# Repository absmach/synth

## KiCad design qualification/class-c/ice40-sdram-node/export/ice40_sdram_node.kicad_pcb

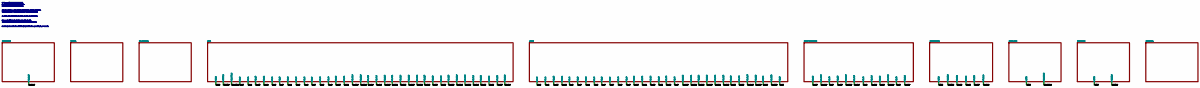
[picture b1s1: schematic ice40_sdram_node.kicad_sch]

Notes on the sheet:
5 V in, max 5.25 V. F1 hold 1.1 A, 16 V.
D1 standoff 6.0 V, above 5.25 V, before Q1.
Q1 P-MOSFET reverse stage, gate to GND.
Soft SDR controller, no hard DDR PHY. VPP_FAST (pin 109) left unconnected.
VCCPLL0/1 from 1.2 V through ferrite L1, 100 nF each and 1 uF bulk.
22 ohm in series at the FPGA end of CLK, CS, RAS, CAS, WE and CKE.
Flash on the iCE40 master SPI pins SS_B, SCK, SDI, SDO.
CRESET_B and CDONE pulled up 10 k. WP and HOLD pulled up 10 k.
D2 3.3 V present. D3 lit when CDONE is high (Q2 buffers the open-drain pin). D4 user LED.

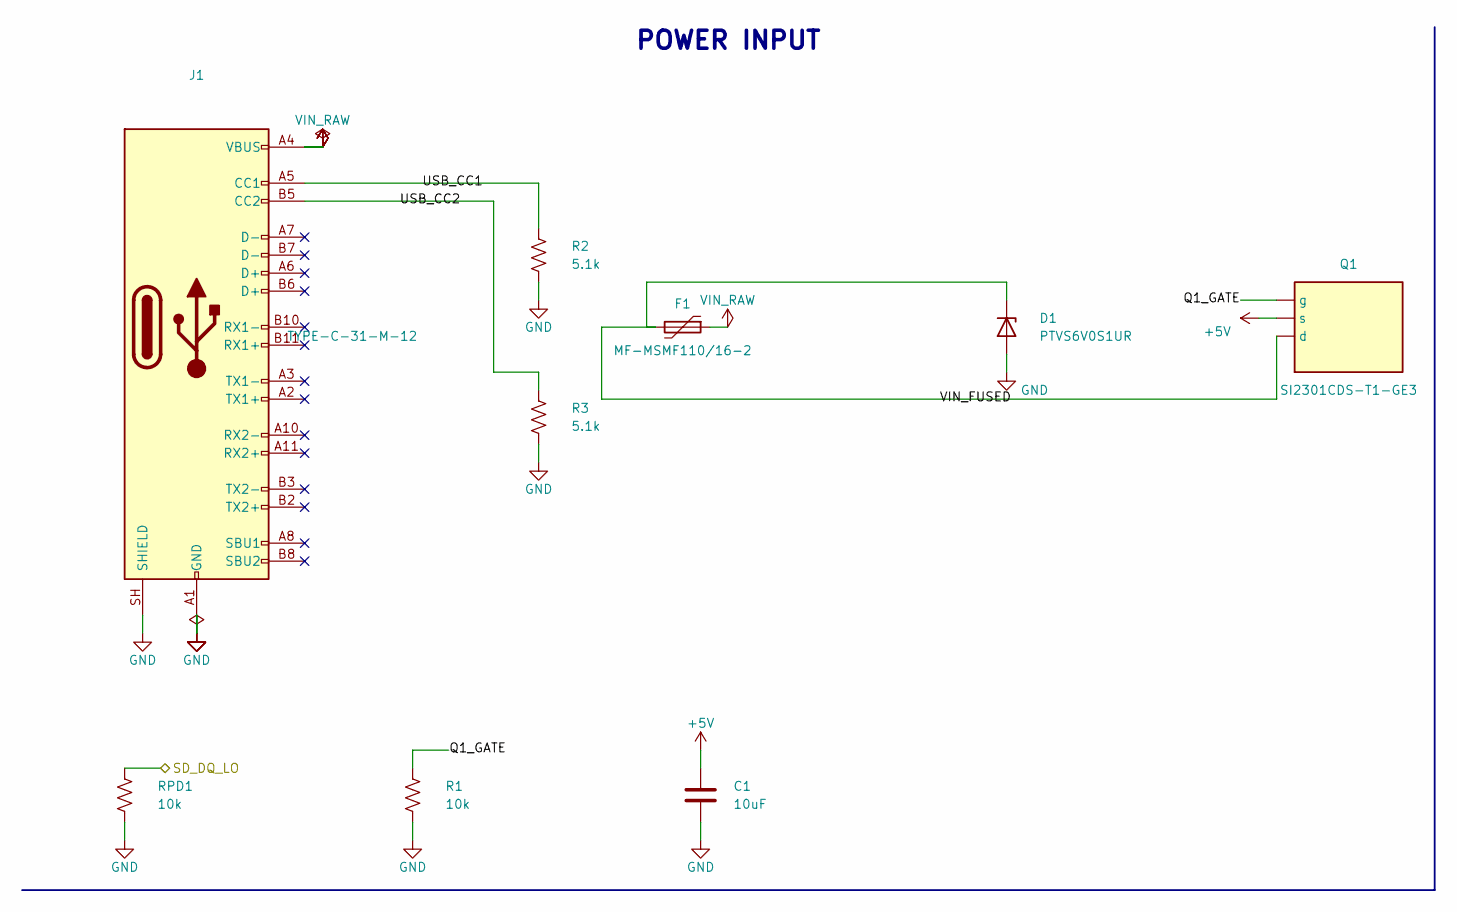
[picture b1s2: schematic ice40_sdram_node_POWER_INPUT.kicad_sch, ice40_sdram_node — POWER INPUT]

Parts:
C1: 10uF; C_0805_2012Metric
D1: PTVS6V0S1UR; Nexperia_CFP3_SOD-123W; MPN PTVS6V0S1UR
F1: MF-MSMF110/16-2; Fuse_1812_4532Metric; MPN MF-MSMF110/16-2; LCSC C210834
J1: TYPE-C-31-M-12; USB_C_Receptacle_HRO_TYPE-C-31-M-12; MPN TYPE-C-31-M-12; LCSC C165948
Q1: SI2301CDS-T1-GE3; SOT-23; MPN SI2301CDS-T1-GE3; LCSC C10487
R1: 10k; R_0603_1608Metric
R2, R3: 5.1k; R_0603_1608Metric
RPD1: 10k; R_0603_1608Metric

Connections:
+5V: C1.1, Q1.2 (s); also elsewhere on the board
GND: C1.2, D1.2 (A), J1.A1 (GND), J1.A12 (GND), J1.B1 (GND), J1.B12 (GND), J1.SH (SHIELD), R1.2, R2.2, R3.2, RPD1.2; also elsewhere on the board
Q1_GATE: Q1.1 (g), R1.1
SD_DQ_LO: RPD1.1; also elsewhere on the board
USB_CC1: J1.A5 (CC1), R2.1
USB_CC2: J1.B5 (CC2), R3.1
VIN_FUSED: D1.1 (K), F1.2, Q1.3 (d)
VIN_RAW: F1.1, J1.A4 (VBUS), J1.A9 (VBUS), J1.B4 (VBUS), J1.B9 (VBUS)

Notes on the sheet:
POWER INPUT

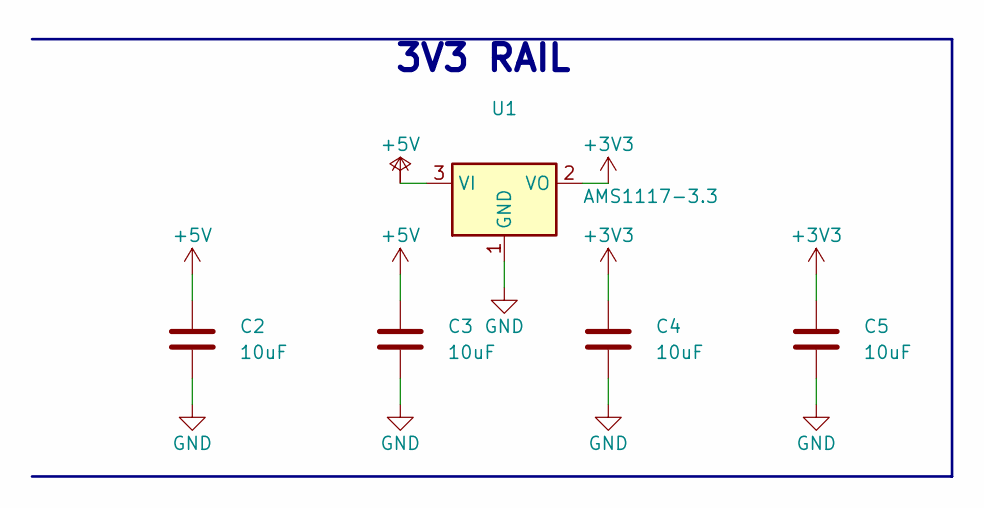
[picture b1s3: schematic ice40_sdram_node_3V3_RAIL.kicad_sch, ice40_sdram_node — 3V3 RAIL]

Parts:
C2, C3, C4, C5: 10uF; C_0805_2012Metric
U1: AMS1117-3.3; SOT-223-3_TabPin2; MPN AMS1117-3.3; LCSC C6186

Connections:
+3V3: C4.1, C5.1, U1.2 (VO); also elsewhere on the board
+5V: C2.1, C3.1, U1.3 (VI); also elsewhere on the board
GND: C2.2, C3.2, C4.2, C5.2, U1.1 (GND); also elsewhere on the board

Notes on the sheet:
3V3 RAIL

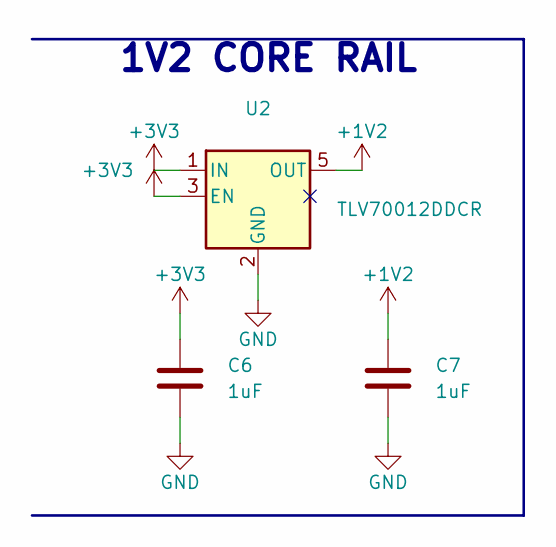
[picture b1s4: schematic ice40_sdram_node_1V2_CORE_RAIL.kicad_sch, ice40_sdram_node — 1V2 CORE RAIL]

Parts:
C6, C7: 1uF; C_0603_1608Metric
U2: TLV70012DDCR; TSOT-23-5; MPN TLV70012DDCR

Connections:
+1V2: C7.1, U2.5 (OUT); also elsewhere on the board
+3V3: C6.1, U2.1 (IN), U2.3 (EN); also elsewhere on the board
GND: C6.2, C7.2, U2.2 (GND); also elsewhere on the board

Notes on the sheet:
1V2 CORE RAIL

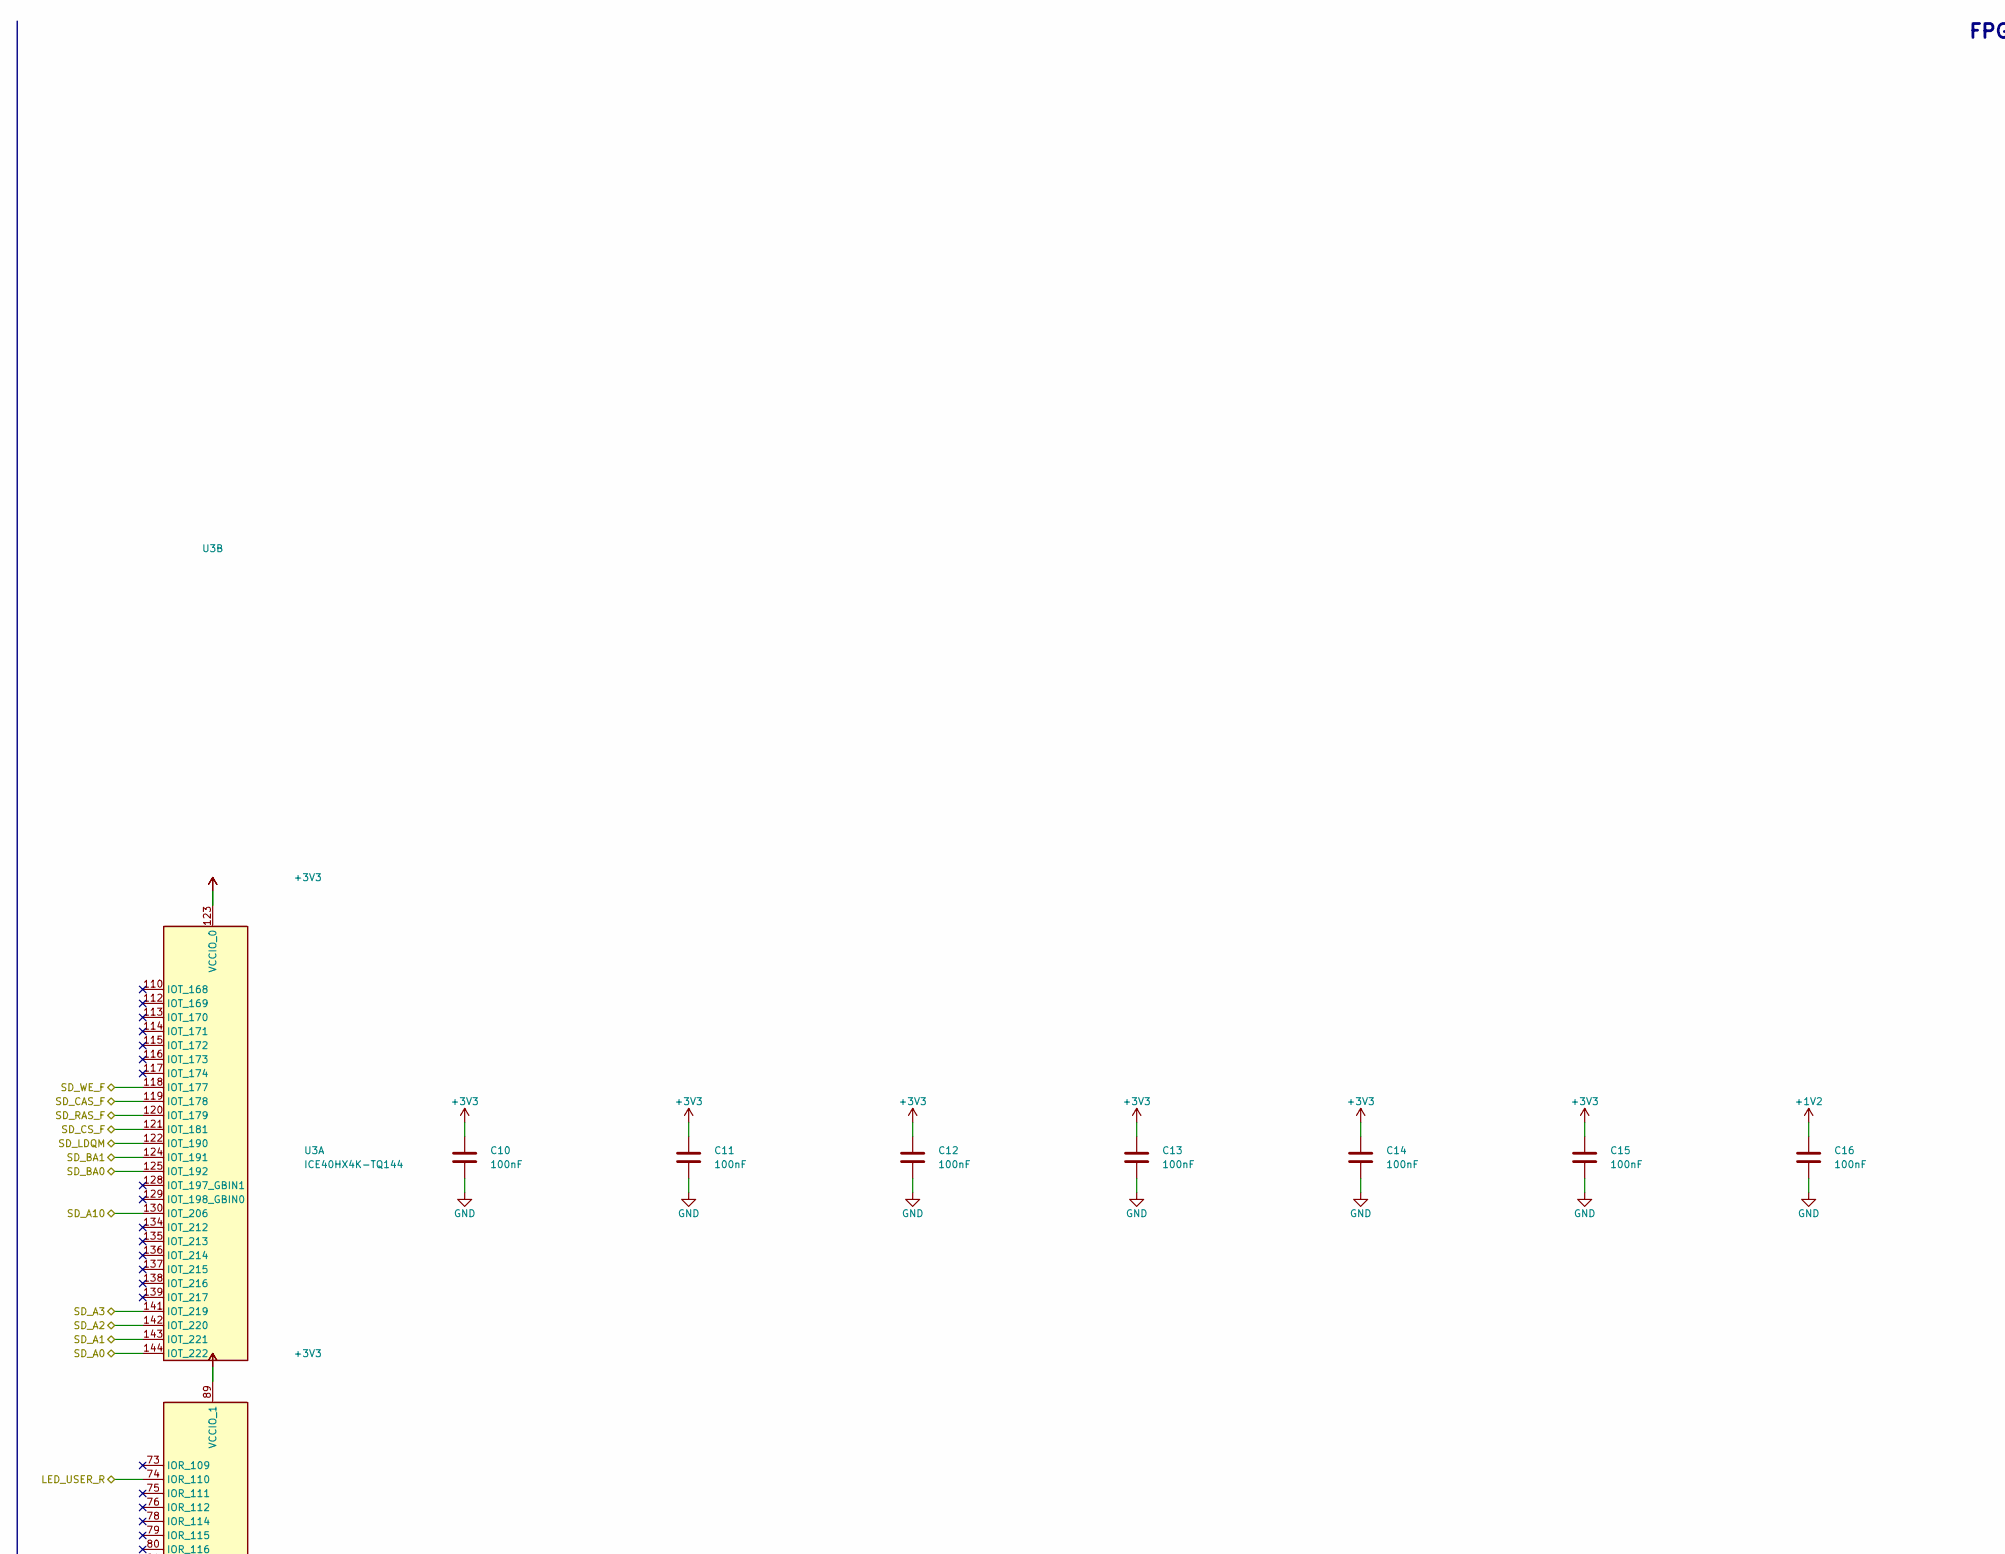
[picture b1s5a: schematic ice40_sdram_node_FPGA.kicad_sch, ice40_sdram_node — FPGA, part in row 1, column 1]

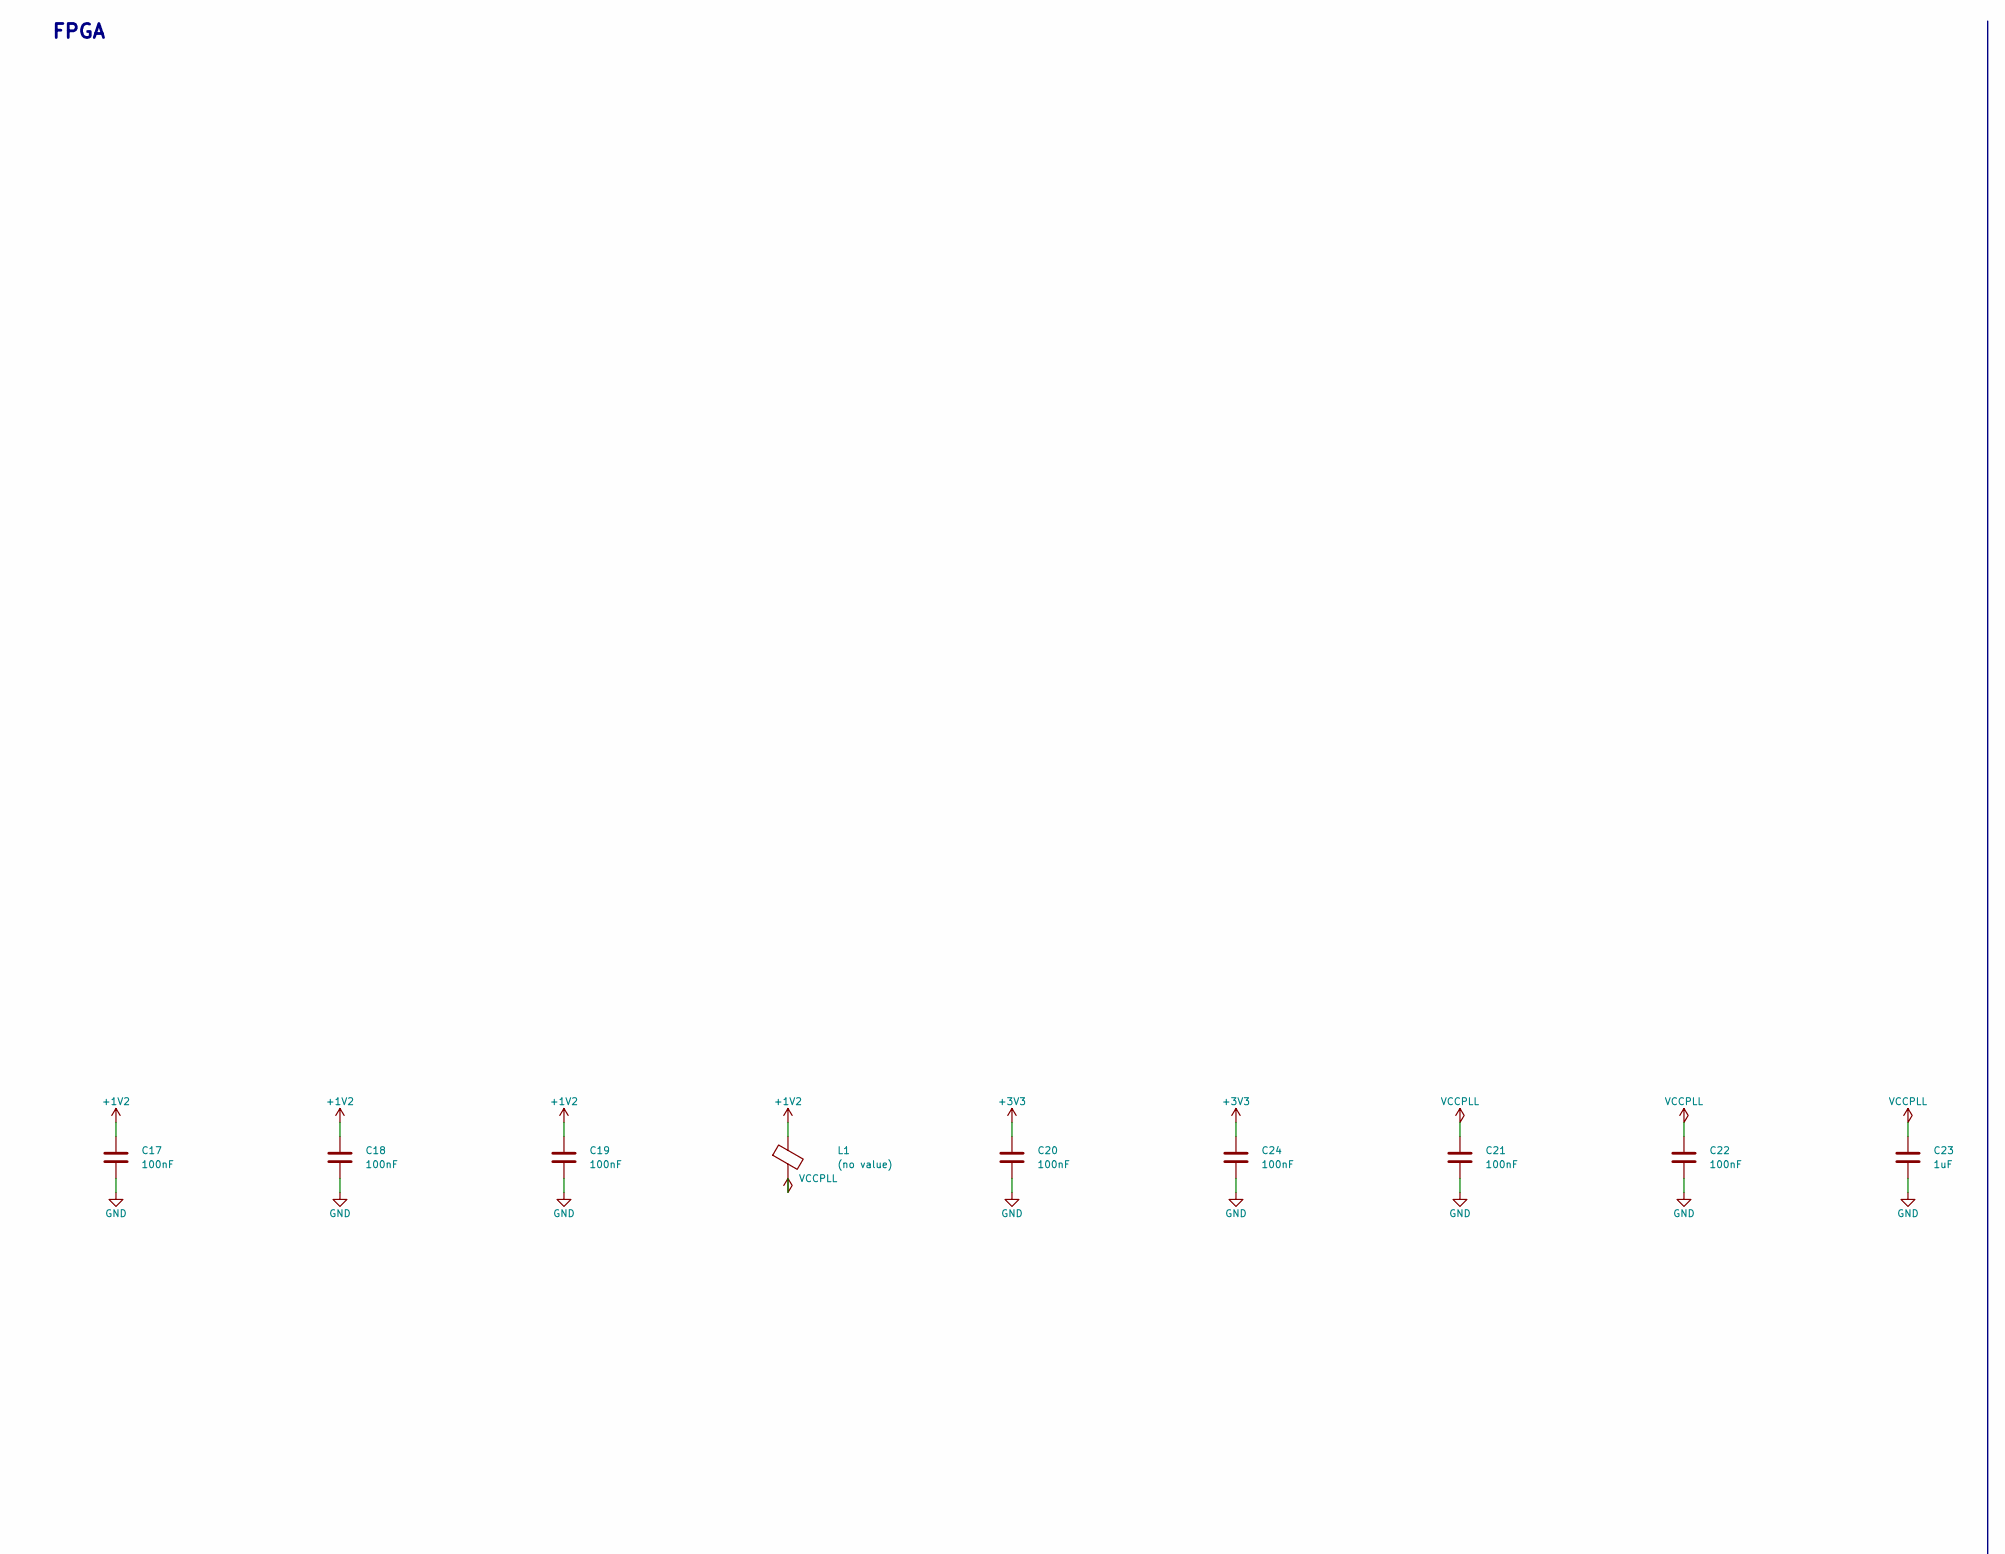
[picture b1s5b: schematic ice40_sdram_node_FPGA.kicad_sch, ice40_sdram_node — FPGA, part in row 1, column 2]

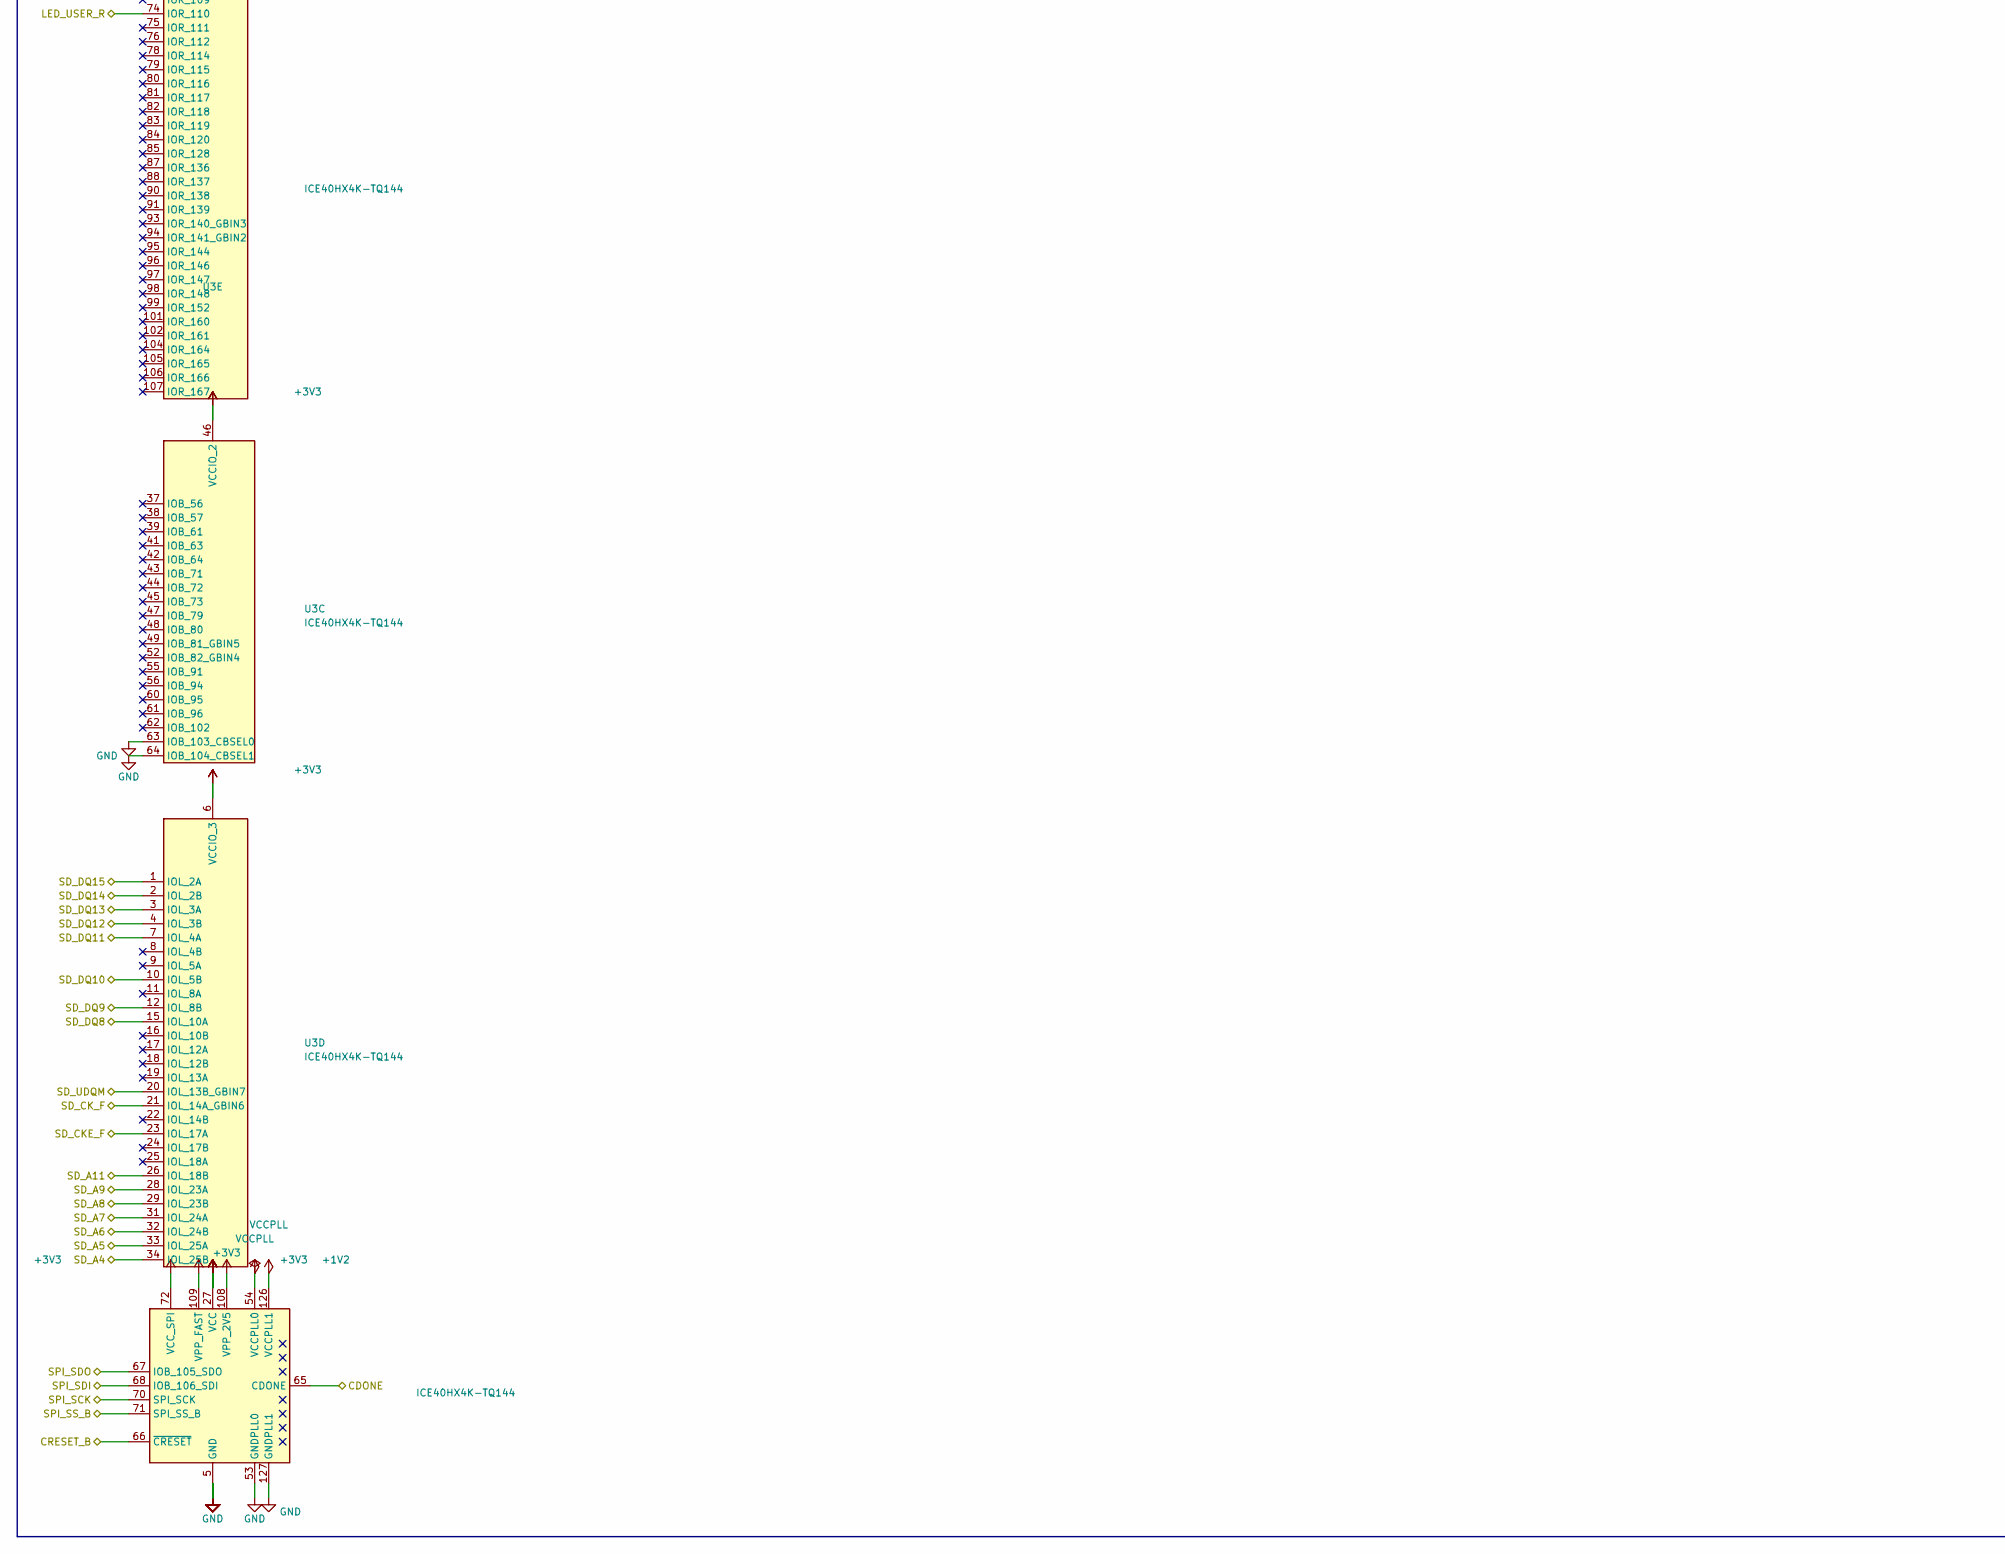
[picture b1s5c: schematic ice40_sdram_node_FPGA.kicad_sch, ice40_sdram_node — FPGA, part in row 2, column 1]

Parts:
C10, C11, C12, C13, C14, C15, C16, C17, C18, C19, C20, C21, C22, C24: 100nF; C_0402_1005Metric
C23: 1uF; C_0603_1608Metric
L1: (no value); L_0603_1608Metric
U3: ICE40HX4K-TQ144; TQFP-144_20x20mm_P0.5mm; MPN ICE40HX4K-TQ144

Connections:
+1V2: C16.1, C17.1, C18.1, C19.1, L1.1, U3.27 (VCC), U3.40 (VCC), U3.92 (VCC), U3.111 (VCC); also elsewhere on the board
+3V3: C10.1, C11.1, C12.1, C13.1, C14.1, C15.1, C20.1, C24.1, U3.6 (VCCIO_3), U3.30 (VCCIO_3), U3.46 (VCCIO_2), U3.57 (VCCIO_2), U3.72 (VCC_SPI), U3.89 (VCCIO_1), U3.100 (VCCIO_1), U3.108 (VPP_2V5), U3.109 (VPP_FAST), U3.123 (VCCIO_0), U3.131 (VCCIO_0); also elsewhere on the board
CDONE: U3.65 (CDONE); also elsewhere on the board
CRESET_B: U3.66 (~CRESET); also elsewhere on the board
GND: C10.2, C11.2, C12.2, C13.2, C14.2, C15.2, C16.2, C17.2, C18.2, C19.2, C20.2, C21.2, C22.2, C23.2, C24.2, U3.5 (GND), U3.13 (GND), U3.14 (GND), U3.53 (GNDPLL0), U3.59 (GND), U3.63 (IOB_103_CBSEL0), U3.64 (IOB_104_CBSEL1), U3.69 (GND), U3.86 (GND), U3.103 (GND), U3.127 (GNDPLL1), U3.132 (GND), U3.140 (GND); also elsewhere on the board
LED_USER_R: U3.74 (IOR_110); also elsewhere on the board
SD_A0: U3.144 (IOT_222); also elsewhere on the board
SD_A1: U3.143 (IOT_221); also elsewhere on the board
SD_A2: U3.142 (IOT_220); also elsewhere on the board
SD_A3: U3.141 (IOT_219); also elsewhere on the board
SD_A4: U3.34 (IOL_25B); also elsewhere on the board
SD_A5: U3.33 (IOL_25A); also elsewhere on the board
SD_A6: U3.32 (IOL_24B); also elsewhere on the board
SD_A7: U3.31 (IOL_24A); also elsewhere on the board
SD_A8: U3.29 (IOL_23B); also elsewhere on the board
SD_A9: U3.28 (IOL_23A); also elsewhere on the board
SD_A10: U3.130 (IOT_206); also elsewhere on the board
SD_A11: U3.26 (IOL_18B); also elsewhere on the board
SD_BA0: U3.125 (IOT_192); also elsewhere on the board
SD_BA1: U3.124 (IOT_191); also elsewhere on the board
SD_CAS_F: U3.119 (IOT_178); also elsewhere on the board
SD_CKE_F: U3.23 (IOL_17A); also elsewhere on the board
SD_CK_F: U3.21 (IOL_14A_GBIN6); also elsewhere on the board
SD_CS_F: U3.121 (IOT_181); also elsewhere on the board
SD_DQ8: U3.15 (IOL_10A); also elsewhere on the board
SD_DQ9: U3.12 (IOL_8B); also elsewhere on the board
SD_DQ10: U3.10 (IOL_5B); also elsewhere on the board
SD_DQ11: U3.7 (IOL_4A); also elsewhere on the board
SD_DQ12: U3.4 (IOL_3B); also elsewhere on the board
SD_DQ13: U3.3 (IOL_3A); also elsewhere on the board
SD_DQ14: U3.2 (IOL_2B); also elsewhere on the board
SD_DQ15: U3.1 (IOL_2A); also elsewhere on the board
SD_LDQM: U3.122 (IOT_190); also elsewhere on the board
SD_RAS_F: U3.120 (IOT_179); also elsewhere on the board
SD_UDQM: U3.20 (IOL_13B_GBIN7); also elsewhere on the board
SD_WE_F: U3.118 (IOT_177); also elsewhere on the board
SPI_SCK: U3.70 (IOB_107_SCK); also elsewhere on the board
SPI_SDI: U3.68 (IOB_106_SDI); also elsewhere on the board
SPI_SDO: U3.67 (IOB_105_SDO); also elsewhere on the board
SPI_SS_B: U3.71 (IOB_108_SS); also elsewhere on the board
VCCPLL: C21.1, C22.1, C23.1, L1.2, U3.54 (VCCPLL0), U3.126 (VCCPLL1)

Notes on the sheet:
FPGA

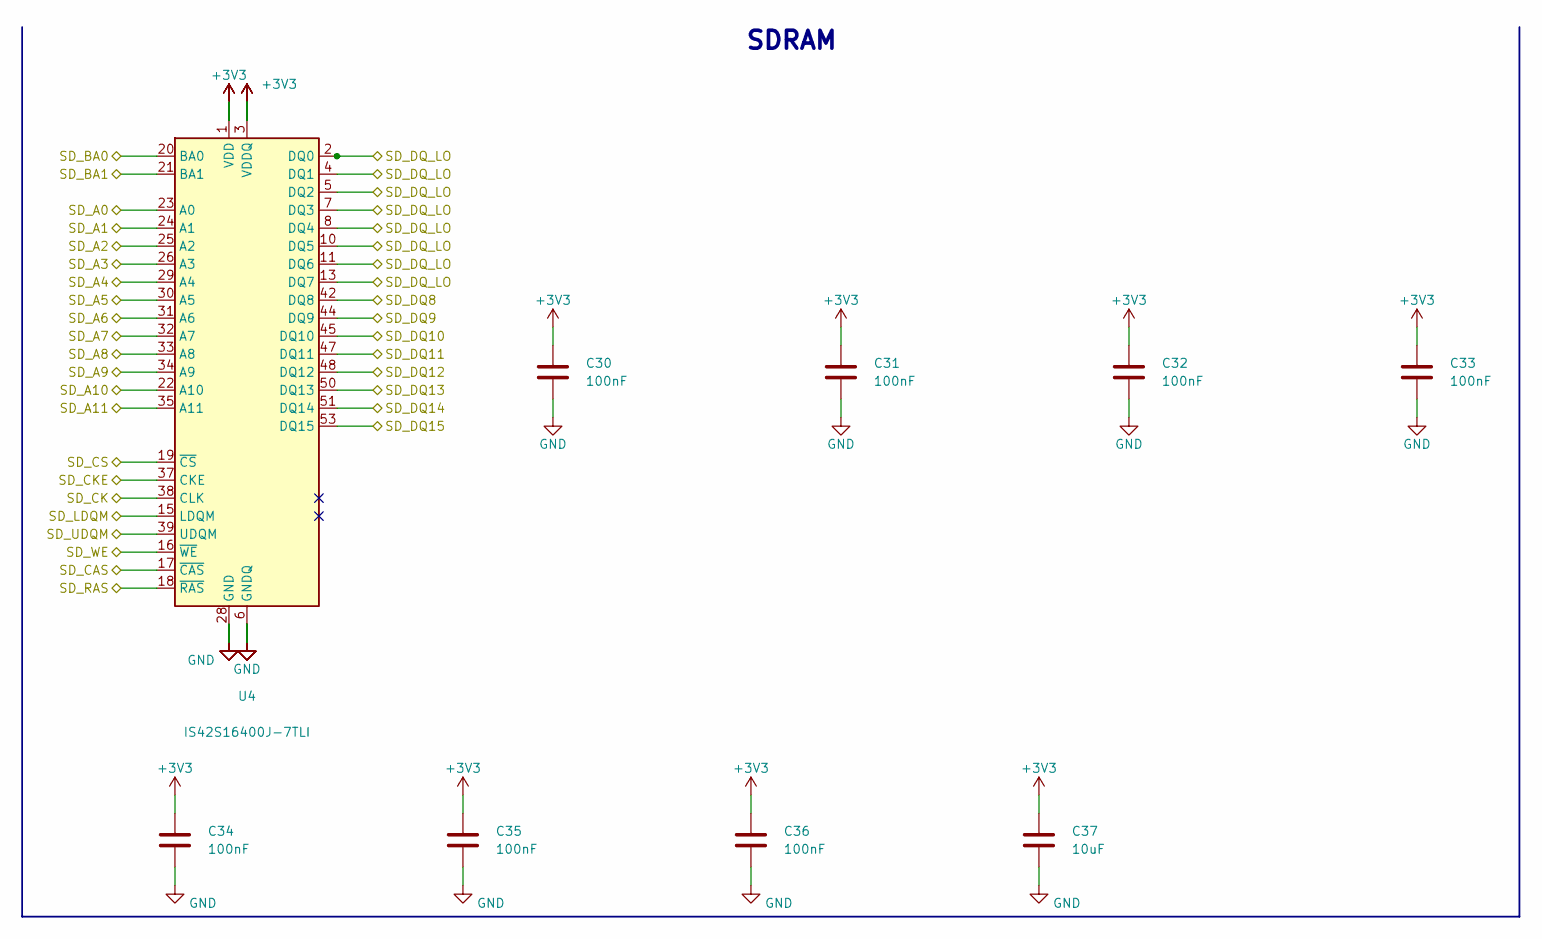
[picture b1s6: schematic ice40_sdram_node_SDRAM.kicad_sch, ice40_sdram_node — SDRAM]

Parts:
C30, C31, C32, C33, C34, C35, C36: 100nF; C_0402_1005Metric
C37: 10uF; C_0805_2012Metric
U4: IS42S16400J-7TLI; TSOP-II-54_22.2x10.16mm_P0.8mm; MPN IS42S16400J-7TLI

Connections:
+3V3: C30.1, C31.1, C32.1, C33.1, C34.1, C35.1, C36.1, C37.1, U4.1 (VDD), U4.3 (VDDQ), U4.9 (VDDQ), U4.14 (VDD), U4.27 (VDD), U4.43 (VDDQ), U4.49 (VDDQ); also elsewhere on the board
GND: C30.2, C31.2, C32.2, C33.2, C34.2, C35.2, C36.2, C37.2, U4.6 (GNDQ), U4.12 (GNDQ), U4.28 (GND), U4.41 (GND), U4.46 (GNDQ), U4.52 (GNDQ), U4.54 (GND); also elsewhere on the board
SD_A0: U4.23 (A0); also elsewhere on the board
SD_A1: U4.24 (A1); also elsewhere on the board
SD_A2: U4.25 (A2); also elsewhere on the board
SD_A3: U4.26 (A3); also elsewhere on the board
SD_A4: U4.29 (A4); also elsewhere on the board
SD_A5: U4.30 (A5); also elsewhere on the board
SD_A6: U4.31 (A6); also elsewhere on the board
SD_A7: U4.32 (A7); also elsewhere on the board
SD_A8: U4.33 (A8); also elsewhere on the board
SD_A9: U4.34 (A9); also elsewhere on the board
SD_A10: U4.22 (A10); also elsewhere on the board
SD_A11: U4.35 (A11); also elsewhere on the board
SD_BA0: U4.20 (BA0); also elsewhere on the board
SD_BA1: U4.21 (BA1); also elsewhere on the board
SD_CAS: U4.17 (~CAS); also elsewhere on the board
SD_CK: U4.38 (CLK); also elsewhere on the board
SD_CKE: U4.37 (CKE); also elsewhere on the board
SD_CS: U4.19 (~CS); also elsewhere on the board
SD_DQ8: U4.42 (DQ8); also elsewhere on the board
SD_DQ9: U4.44 (DQ9); also elsewhere on the board
SD_DQ10: U4.45 (DQ10); also elsewhere on the board
SD_DQ11: U4.47 (DQ11); also elsewhere on the board
SD_DQ12: U4.48 (DQ12); also elsewhere on the board
SD_DQ13: U4.50 (DQ13); also elsewhere on the board
SD_DQ14: U4.51 (DQ14); also elsewhere on the board
SD_DQ15: U4.53 (DQ15); also elsewhere on the board
SD_DQ_LO: U4.2 (DQ0), U4.4 (DQ1), U4.5 (DQ2), U4.7 (DQ3), U4.8 (DQ4), U4.10 (DQ5), U4.11 (DQ6), U4.13 (DQ7); also elsewhere on the board
SD_LDQM: U4.15 (LDQM); also elsewhere on the board
SD_RAS: U4.18 (~RAS); also elsewhere on the board
SD_UDQM: U4.39 (UDQM); also elsewhere on the board
SD_WE: U4.16 (~WE); also elsewhere on the board

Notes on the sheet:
SDRAM

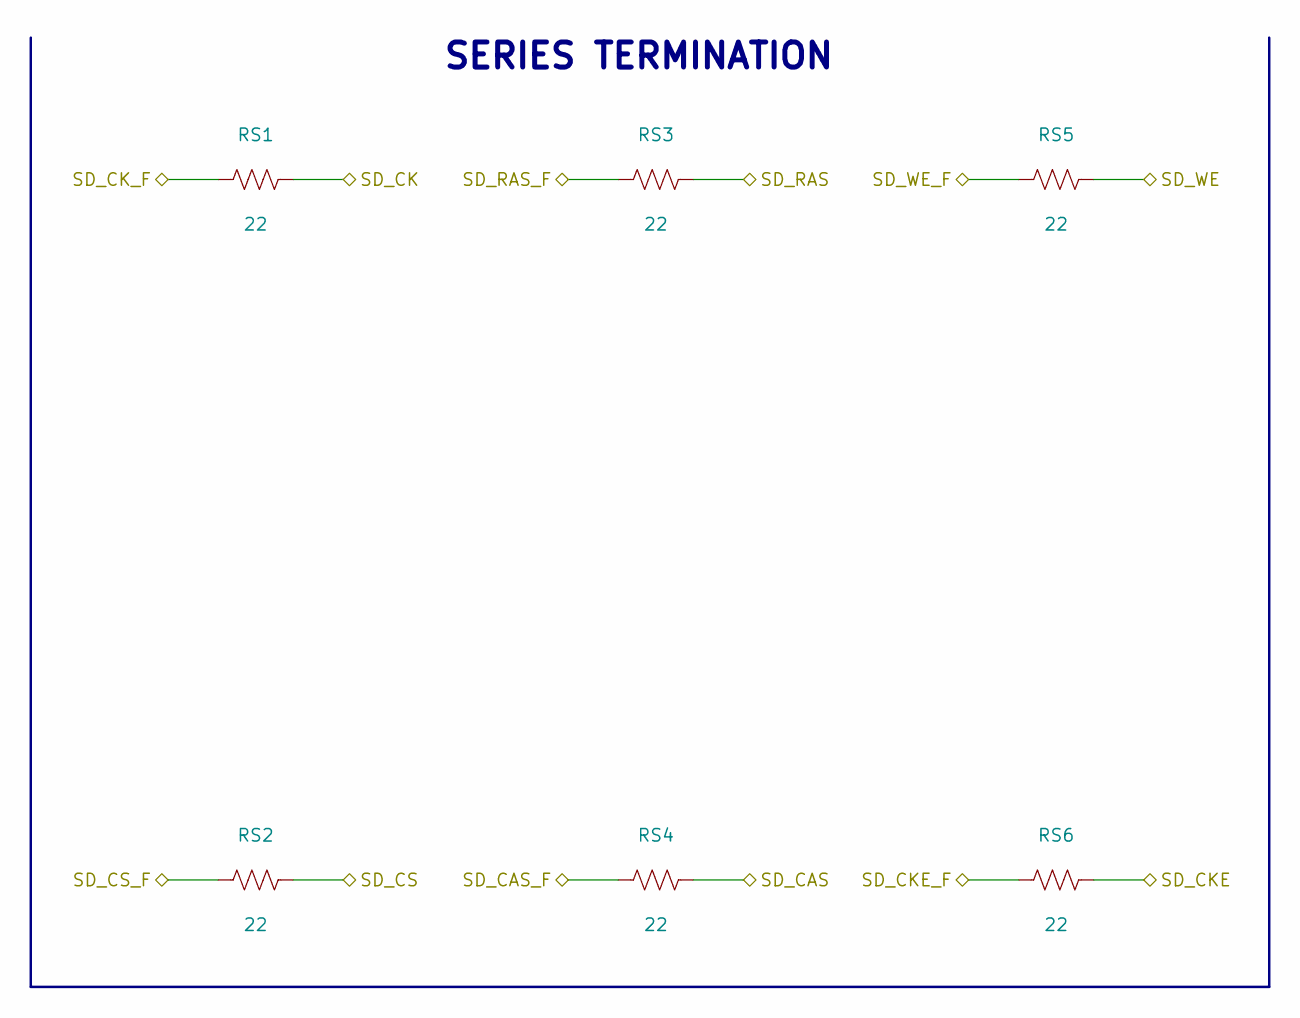
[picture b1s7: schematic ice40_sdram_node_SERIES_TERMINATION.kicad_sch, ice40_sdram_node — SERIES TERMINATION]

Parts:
RS1, RS2, RS3, RS4, RS5, RS6: 22; R_0402_1005Metric

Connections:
SD_CAS: RS4.2; also elsewhere on the board
SD_CAS_F: RS4.1; also elsewhere on the board
SD_CK: RS1.2; also elsewhere on the board
SD_CKE: RS6.2; also elsewhere on the board
SD_CKE_F: RS6.1; also elsewhere on the board
SD_CK_F: RS1.1; also elsewhere on the board
SD_CS: RS2.2; also elsewhere on the board
SD_CS_F: RS2.1; also elsewhere on the board
SD_RAS: RS3.2; also elsewhere on the board
SD_RAS_F: RS3.1; also elsewhere on the board
SD_WE: RS5.2; also elsewhere on the board
SD_WE_F: RS5.1; also elsewhere on the board

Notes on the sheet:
SERIES TERMINATION

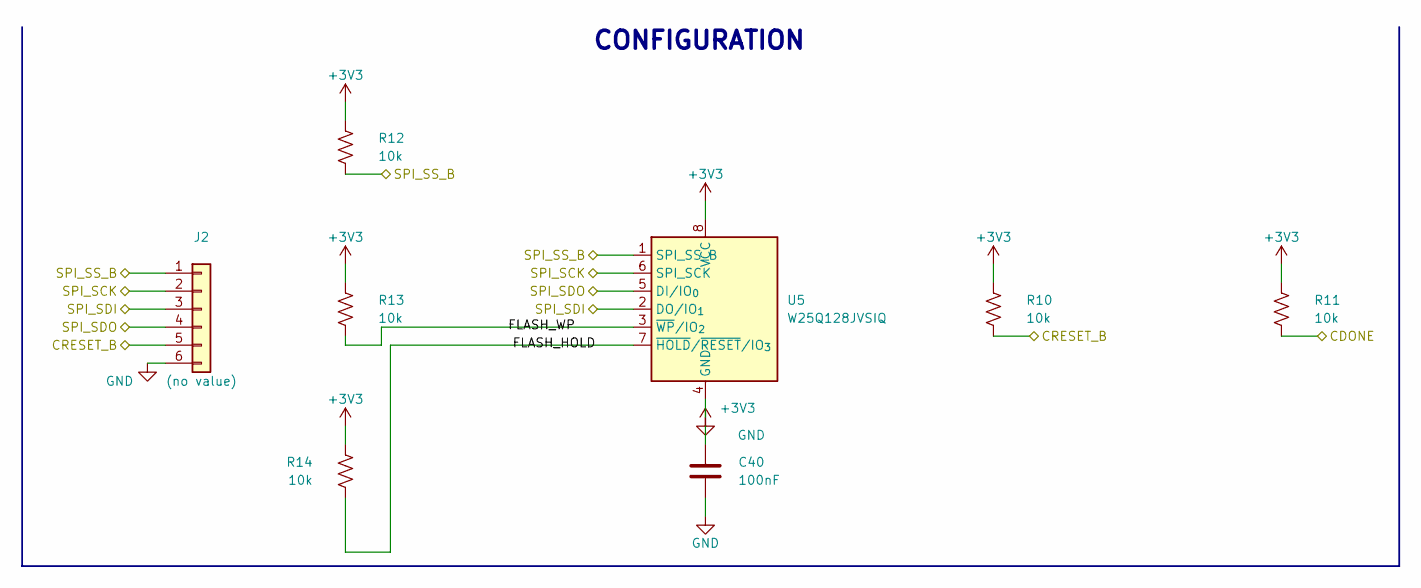
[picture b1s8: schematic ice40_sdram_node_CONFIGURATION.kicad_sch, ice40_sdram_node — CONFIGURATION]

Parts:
C40: 100nF; C_0603_1608Metric
J2: (no value); PinHeader_1x06_P2.54mm_Vertical
R10, R11, R12, R13, R14: 10k; R_0603_1608Metric
U5: W25Q128JVSIQ; SOIC-8_5.3x5.3mm_P1.27mm; MPN W25Q128JVSIQ; LCSC C97521

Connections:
+3V3: C40.1, R10.1, R11.1, R12.1, R13.1, R14.1, U5.8 (VCC); also elsewhere on the board
CDONE: R11.2; also elsewhere on the board
CRESET_B: J2.5, R10.2; also elsewhere on the board
FLASH_HOLD: R14.2, U5.7 (~HOLD/~RESET/IO_{3})
FLASH_WP: R13.2, U5.3 (~WP/IO_{2})
GND: C40.2, J2.6, U5.4 (GND); also elsewhere on the board
SPI_SCK: J2.2, U5.6 (CLK); also elsewhere on the board
SPI_SDI: J2.3, U5.2 (DO/IO_{1}); also elsewhere on the board
SPI_SDO: J2.4, U5.5 (DI/IO_{0}); also elsewhere on the board
SPI_SS_B: J2.1, R12.2, U5.1 (~CS); also elsewhere on the board

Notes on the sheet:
CONFIGURATION

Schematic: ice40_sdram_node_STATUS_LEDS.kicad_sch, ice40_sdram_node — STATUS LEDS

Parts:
D2: 0603-RED; LED_0603_1608Metric; MPN 0603-RED; LCSC C2286
D3, D4: 0603-GREEN; LED_0603_1608Metric; MPN 0603-GREEN; LCSC C72043
Q2: AO3400A; SOT-23; MPN AO3400A
R20, R21, R22: 1k; R_0603_1608Metric

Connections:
+3V3: R20.1, R21.1; also elsewhere on the board
CDONE: Q2.1 (G); also elsewhere on the board
GND: D2.1 (K), D4.1 (K), Q2.2 (S); also elsewhere on the board
LED_DONE_A: D3.2 (A), R21.2
LED_DONE_K: D3.1 (K), Q2.3 (D)
LED_PWR: D2.2 (A), R20.2
LED_USER_A: D4.2 (A), R22.2
LED_USER_R: R22.1; also elsewhere on the board

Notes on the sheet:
STATUS LEDS

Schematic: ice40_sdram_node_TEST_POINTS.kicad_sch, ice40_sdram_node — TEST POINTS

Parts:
TP1, TP2, TP3, TP4, TP5, TP6, TP7: (no value); TestPoint_Pad_D1.5mm

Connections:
+1V2: TP3.1; also elsewhere on the board
+3V3: TP2.1; also elsewhere on the board
+5V: TP1.1; also elsewhere on the board
CDONE: TP5.1; also elsewhere on the board
CRESET_B: TP6.1; also elsewhere on the board
GND: TP4.1, TP7.1; also elsewhere on the board

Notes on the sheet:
TEST POINTS

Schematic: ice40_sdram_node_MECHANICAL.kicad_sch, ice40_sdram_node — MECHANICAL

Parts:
H1, H2: (no value); MountingHole_2.5mm

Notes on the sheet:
MECHANICAL
